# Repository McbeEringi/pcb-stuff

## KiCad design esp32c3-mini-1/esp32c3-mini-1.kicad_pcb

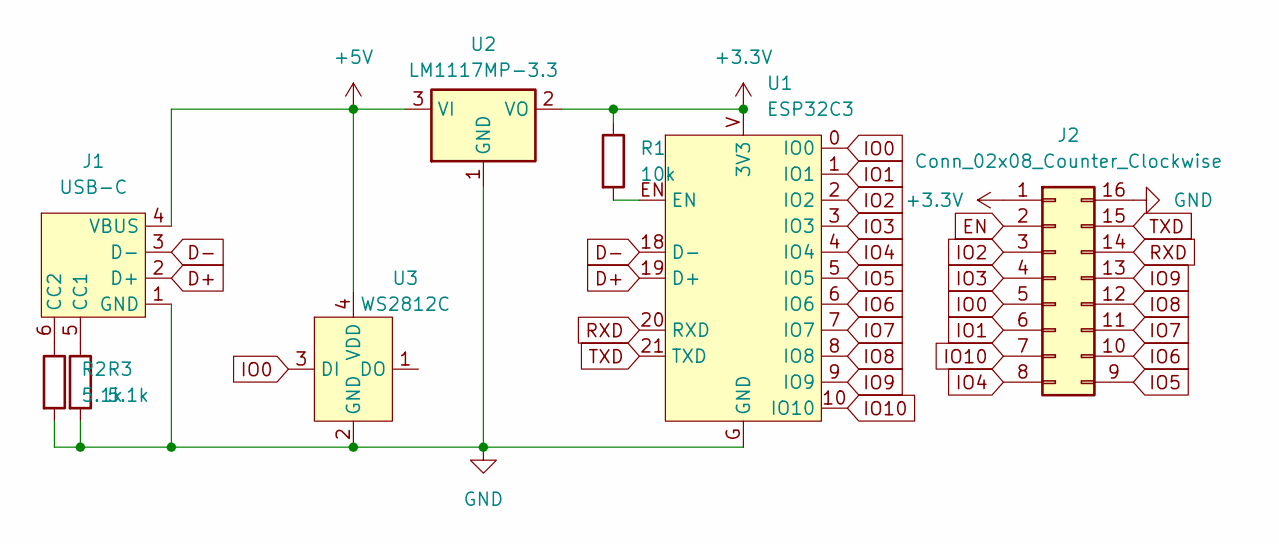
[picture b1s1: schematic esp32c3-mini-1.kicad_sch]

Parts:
J1: USB-C
J2: Conn_02x08_Counter_Clockwise; DIP-16_W7.62mm
R1: 10k; R_0603_1608Metric
R2, R3: 5.1k; R_0603_1608Metric
U1: ESP32C3; ESP32C3-MINI-1
U2: LM1117MP-3.3; SOT-223-3_TabPin2
U3: WS2812C; WS2812C-2020

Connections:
+3.3V: J2.1, R1.1, U1.V (3V3), U2.2 (VO)
+5V: J1.4 (VBUS), U2.3 (VI), U3.4 (VDD)
D+: J1.2 (D+), U1.19 (D+)
D-: J1.3 (D-), U1.18 (D-)
EN: J2.2
GND: J1.1 (GND), J2.16, R2.2, R3.2, U1.G (GND), U2.1 (GND), U3.2 (GND)
IO0: J2.5, U1.0 (IO0), U3.3 (DI)
IO1: J2.6, U1.1 (IO1)
IO2: J2.3, U1.2 (IO2)
IO3: J2.4, U1.3 (IO3)
IO4: J2.8, U1.4 (IO4)
IO5: J2.9, U1.5 (IO5)
IO6: J2.10, U1.6 (IO6)
IO7: J2.11, U1.7 (IO7)
IO8: J2.12, U1.8 (IO8)
IO9: J2.13, U1.9 (IO9)
IO10: J2.7, U1.10 (IO10)
unnamed: J1.5 (CC1), R3.1
unnamed: J1.6 (CC2), R2.1
unnamed: R1.2, U1.EN
RXD: J2.14, U1.20 (RXD)
TXD: J2.15, U1.21 (TXD)

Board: 2 copper layers, 8 parts (0 on the bottom side), 21 nets, no tracks yet.

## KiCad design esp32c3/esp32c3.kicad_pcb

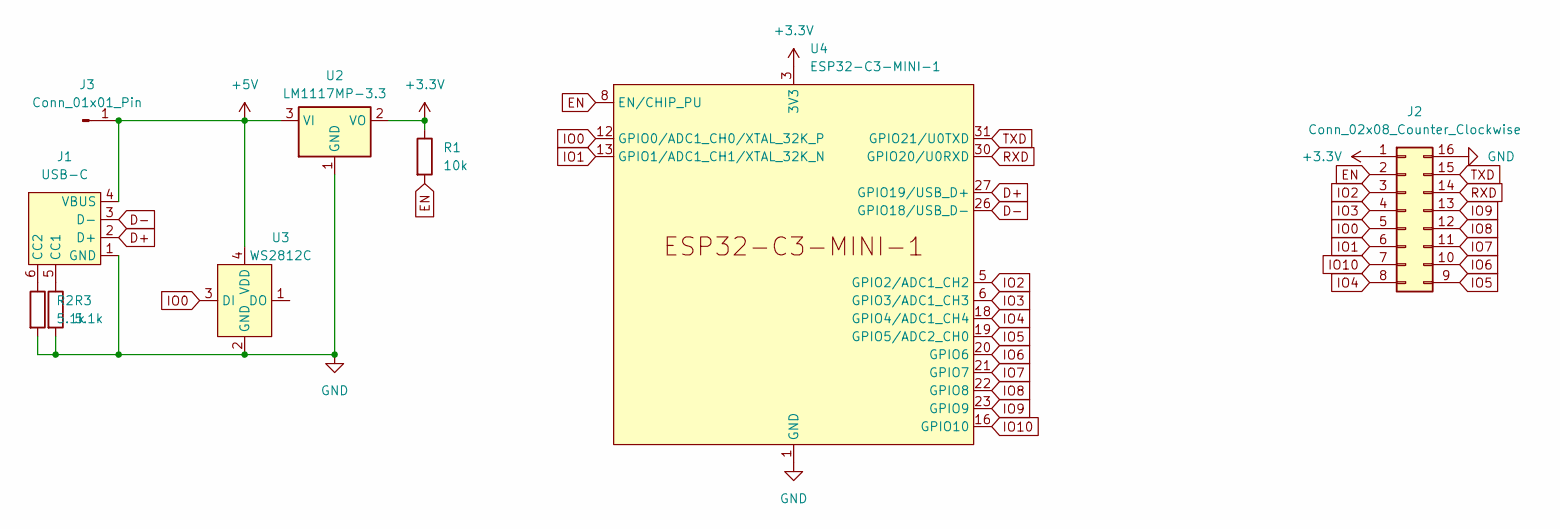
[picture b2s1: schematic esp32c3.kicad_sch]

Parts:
J1: USB-C
J2: Conn_02x08_Counter_Clockwise; DIP-16_W10.16mm
J3: Conn_01x01_Pin; PinHeader_1x01_P2.54mm_Vertical
R1: 10k; R_0603_1608Metric
R2, R3: 5.1k; R_0603_1608Metric
U2: LM1117MP-3.3; SOT-223-3_TabPin2
U3: WS2812C; WS2812C-2020
U4: ESP32-C3-MINI-1

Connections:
+3.3V: J2.1, R1.1, U2.2 (VO), U4.3 (3V3)
+5V: J1.4 (VBUS), J3.1, U2.3 (VI), U3.4 (VDD)
D+: J1.2 (D+), U4.27 (GPIO19/USB_D+)
D-: J1.3 (D-), U4.26 (GPIO18/USB_D-)
EN: J2.2, R1.2, U4.8 (EN/CHIP_PU)
GND: J1.1 (GND), J2.16, R2.2, R3.2, U2.1 (GND), U3.2 (GND), U4.1 (GND), U4.2 (GND), U4.11 (GND), U4.14 (GND), U4.36 (GND), U4.37 (GND), U4.38 (GND), U4.39 (GND), U4.40 (GND), U4.41 (GND), U4.42 (GND), U4.43 (GND), U4.44 (GND), U4.45 (GND), U4.46 (GND), U4.47 (GND), U4.48 (GND), U4.49 (GND), U4.50 (GND), U4.51 (GND), U4.52 (GND), U4.53 (GND)
IO0: J2.5, U3.3 (DI), U4.12 (GPIO0/ADC1_CH0/XTAL_32K_P)
IO1: J2.6, U4.13 (GPIO1/ADC1_CH1/XTAL_32K_N)
IO2: J2.3, U4.5 (GPIO2/ADC1_CH2)
IO3: J2.4, U4.6 (GPIO3/ADC1_CH3)
IO4: J2.8, U4.18 (GPIO4/ADC1_CH4)
IO5: J2.9, U4.19 (GPIO5/ADC2_CH0)
IO6: J2.10, U4.20 (GPIO6)
IO7: J2.11, U4.21 (GPIO7)
IO8: J2.12, U4.22 (GPIO8)
IO9: J2.13, U4.23 (GPIO9)
IO10: J2.7, U4.16 (GPIO10)
unnamed: J1.5 (CC1), R3.1
unnamed: J1.6 (CC2), R2.1
RXD: J2.14, U4.30 (GPIO20/U0RXD)
TXD: J2.15, U4.31 (GPIO21/U0TXD)

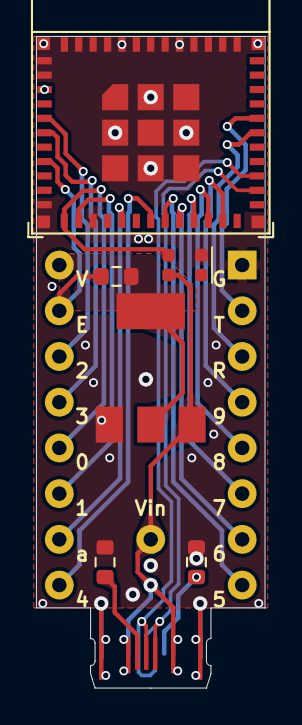
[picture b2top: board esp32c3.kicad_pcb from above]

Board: 2 copper layers, 12.7 x 36.2 mm, 9 parts (0 on the bottom side), 21 nets.

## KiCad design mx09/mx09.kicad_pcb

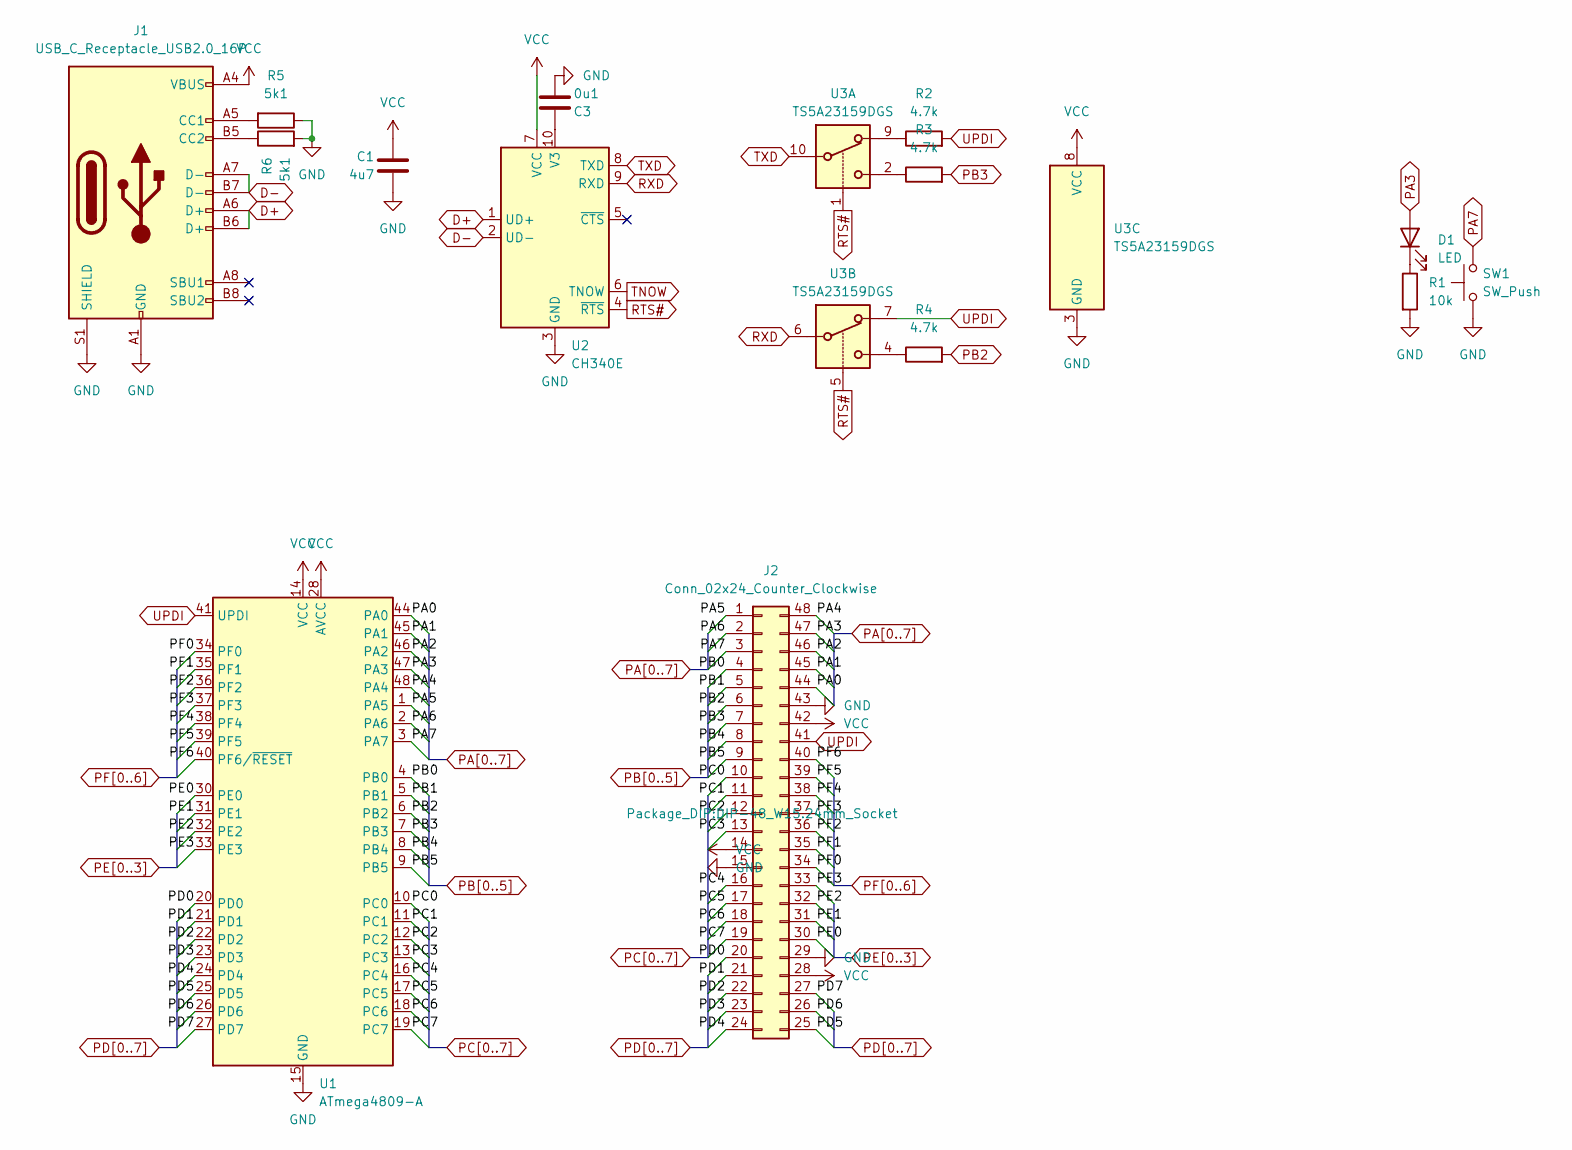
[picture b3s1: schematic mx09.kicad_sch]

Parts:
C1: 4u7; C_0603_1608Metric
C3: 0u1; C_0603_1608Metric
D1: LED; LED_0603_1608Metric
J1: USB_C_Receptacle_USB2.0_16P; USB_C_Receptacle_GCT_USB4105-xx-A_16P_TopMnt_Horizontal
J2: Conn_02x24_Counter_Clockwise; DIP-48_W15.24mm_Socket
R1: 10k; R_0603_1608Metric
R2, R3, R4: 4.7k; R_0603_1608Metric
R5, R6: 5k1; R_0603_1608Metric
SW1: SW_Push; alps-skrp
U1: ATmega4809-A; TQFP-48_7x7mm_P0.5mm
U2: CH340E; MSOP-10_3x3mm_P0.5mm
U3: TS5A23159DGS; VSSOP-10_3x3mm_P0.5mm

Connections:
D+: J1.A6 (D+), J1.B6 (D+), U2.1 (UD+)
D-: J1.A7 (D-), J1.B7 (D-), U2.2 (UD-)
GND: C1.2, C3.2, J1.A1 (GND), J1.A12 (GND), J1.B1 (GND), J1.B12 (GND), J1.S1 (SHIELD), J2.15, J2.29, J2.43, R1.2, R5.1, R6.2, SW1.1, U1.15 (GND), U1.29 (GND), U1.43 (GND), U2.3 (GND), U3.3 (GND)
unnamed: D1.1 (K), R1.1
unnamed: J1.A5 (CC1), R5.2
unnamed: J1.B5 (CC2), R6.1
unnamed: R2.1, U3.9
unnamed: R3.1, U3.2
unnamed: R4.1, U3.4
unnamed: C3.1, U2.10 (V3)
PA0: J2.44, U1.44 (PA0)
PA1: J2.45, U1.45 (PA1)
PA2: J2.46, U1.46 (PA2)
PA3: D1.2 (A), J2.47, U1.47 (PA3)
PA4: J2.48, U1.48 (PA4)
PA5: J2.1, U1.1 (PA5)
PA6: J2.2, U1.2 (PA6)
PA7: J2.3, SW1.2, U1.3 (PA7)
PB0: J2.4, U1.4 (PB0)
PB1: J2.5, U1.5 (PB1)
PB2: J2.6, R4.2, U1.6 (PB2)
PB3: J2.7, R3.2, U1.7 (PB3)
PB4: J2.8, U1.8 (PB4)
PB5: J2.9, U1.9 (PB5)
PC0: J2.10, U1.10 (PC0)
PC1: J2.11, U1.11 (PC1)
PC2: J2.12, U1.12 (PC2)
PC3: J2.13, U1.13 (PC3)
PC4: J2.16, U1.16 (PC4)
PC5: J2.17, U1.17 (PC5)
PC6: J2.18, U1.18 (PC6)
PC7: J2.19, U1.19 (PC7)
PD0: J2.20, U1.20 (PD0)
PD1: J2.21, U1.21 (PD1)
PD2: J2.22, U1.22 (PD2)
PD3: J2.23, U1.23 (PD3)
PD4: J2.24, U1.24 (PD4)
PD5: J2.25, U1.25 (PD5)
PD6: J2.26, U1.26 (PD6)
PD7: J2.27, U1.27 (PD7)
PE0: J2.30, U1.30 (PE0)
PE1: J2.31, U1.31 (PE1)
PE2: J2.32, U1.32 (PE2)
PE3: J2.33, U1.33 (PE3)
PF0: J2.34, U1.34 (PF0)
PF1: J2.35, U1.35 (PF1)
PF2: J2.36, U1.36 (PF2)
PF3: J2.37, U1.37 (PF3)
PF4: J2.38, U1.38 (PF4)
PF5: J2.39, U1.39 (PF5)
PF6: J2.40, U1.40 (PF6/~RESET)
RTS#: U2.4 (~RTS), U3.1, U3.5
RXD: U2.9 (RXD), U3.6
TNOW: U2.6 (TNOW)
TXD: U2.8 (TXD), U3.10
UPDI: J2.41, R2.2, U1.41 (UPDI), U3.7
VCC: C1.1, J1.A4 (VBUS), J1.A9 (VBUS), J1.B4 (VBUS), J1.B9 (VBUS), J2.14, J2.28, J2.42, U1.14 (VCC), U1.28 (AVCC), U1.42 (VCC), U2.7 (VCC), U3.8 (VCC)

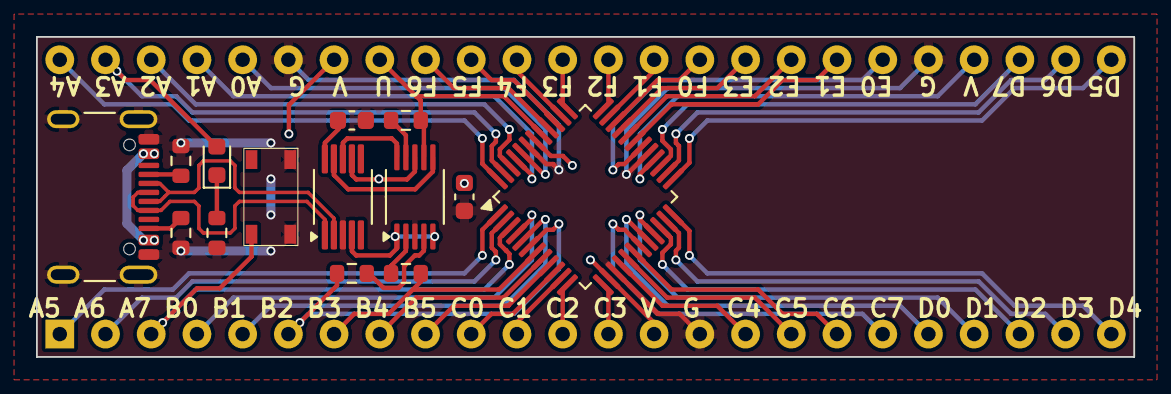
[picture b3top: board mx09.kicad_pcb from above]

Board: 2 copper layers, 61.0 x 17.8 mm, 15 parts (0 on the bottom side), 56 nets.
